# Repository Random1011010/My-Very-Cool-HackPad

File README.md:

# My Very Cool HackPad

A 6-key macropad with a rotary encoder (push-button) and a 128x32 OLED display, built around the Seeed Studio XIAO RP2040. The OLED runs an idle-animated "Luna" sprite that cycles through sit, walk, run, sleep, and work.

## About me

I'm a Grade 10 (going into Grade 11) student, I am interested in aerospace, but I wanted to get real hands-on experience with hardware and PCB design before jumping into anything bigger. This was my first full custom PCB build, so a lot of this project was just learning by doing.

## Inspiration & Challenges

I wanted something I'd actually use, not just a demo board but rather, media controls, screen brightness, and a few shortcuts I use constantly (Spotlight, screenshot, undo/redo). The OLED also mattered to me too, I didn't want it just showing static text, so it runs a small animated character instead.

Most of the challenges were on the PCB and case side, since this was my first time doing either seriously. In KiCad, I had to fix a missing net label on one of the matrix columns, and ran into alignment issues while placing components that took a while to track down. Getting the rotary encoder's footprint right was its own thing.

The case went through a full rebuild. I first modeled it with not a clue how to I would get the keys to line up with the PCB, then rebuilt it in Fusion 360, sketch by sketch, to match Hack Club's submission format, while keeping the board dimensions (84x59.5mm), switch spacing, and heatset insert placement consistent with the original.

On the firmware side, I wrote the QMK code for the matrix, the encoder (volume normally, brightness when you hold the encoder's button), and the OLED animation, I adapted an open-source Luna sprite animation to loop continuously instead of reacting to typing, since I wanted it to feel more like a little idle character than a status display.
(Hopefully it works)

## Features

- 6-key matrix (2 rows x 3 columns)
- Rotary encoder with push-button:
  - Rotate: volume up/down (default)
  - Hold + rotate: screen brightness up/down
  - Short tap: play/pause
- 128x32 I2C OLED with an idle-animated Luna sprite
- QMK firmware, fully open source

## Bill of Materials (BOM)

| Part | Qty | Unit Cost | Total | Notes |
|---|---|---|---|---|
| Seeed Studio XIAO RP2040 | 1 | $5.00 | $5.00 | Main MCU |
| Cherry MX-style switches | 6 | $0.35 | $2.10 | |
| Keycaps | 6 | $0.30 | $1.80 | |
| Rotary encoder (EC11) with push-button | 1 | $0.90 | $0.90 | |
| 128x32 I2C OLED display (SSD1306) | 1 | $5.90 | $5.90 | |
| Custom PCB | 1 | ~$5.00 | $5.00 | 2-layer, JLCPCB/similar, price for small qty |
| 3D printed case | 1 | ~$3.00 | $3.00 | Filament cost estimate |
| M3 heatset inserts | 6 | $0.10 | $0.60 | |
| Diodes | 6 | $0.05 | $0.30 | 1N4148, one per switch |
| **Total** | | | **~$24.60** | |

## Pinout

| Function | Pin |
|---|---|
| Matrix rows | GP26, GP27 |
| Matrix cols | GP29, GP0, GP3 |
| Encoder A/B | GP2, GP1 |
| Encoder switch | GP28 |
| OLED SDA | GP6 |
| OLED SCL | GP7 |

## Photos

**Exploded View**

**Schematic:**

**PCB:**

**Case:**

**Firmware**
Written in QMK. Full source is in the `firmware/` folder — see [`firmware/myverycoolpad/readme.md`](firmware/myverycoolpad/readme.md) for build/flash instructions.

**Status**
Parts haven't arrived yet, so the physical build and OLED orientation are untested. Firmware compiles cleanly with `qmk compile -kb myverycoolpad -km default`.

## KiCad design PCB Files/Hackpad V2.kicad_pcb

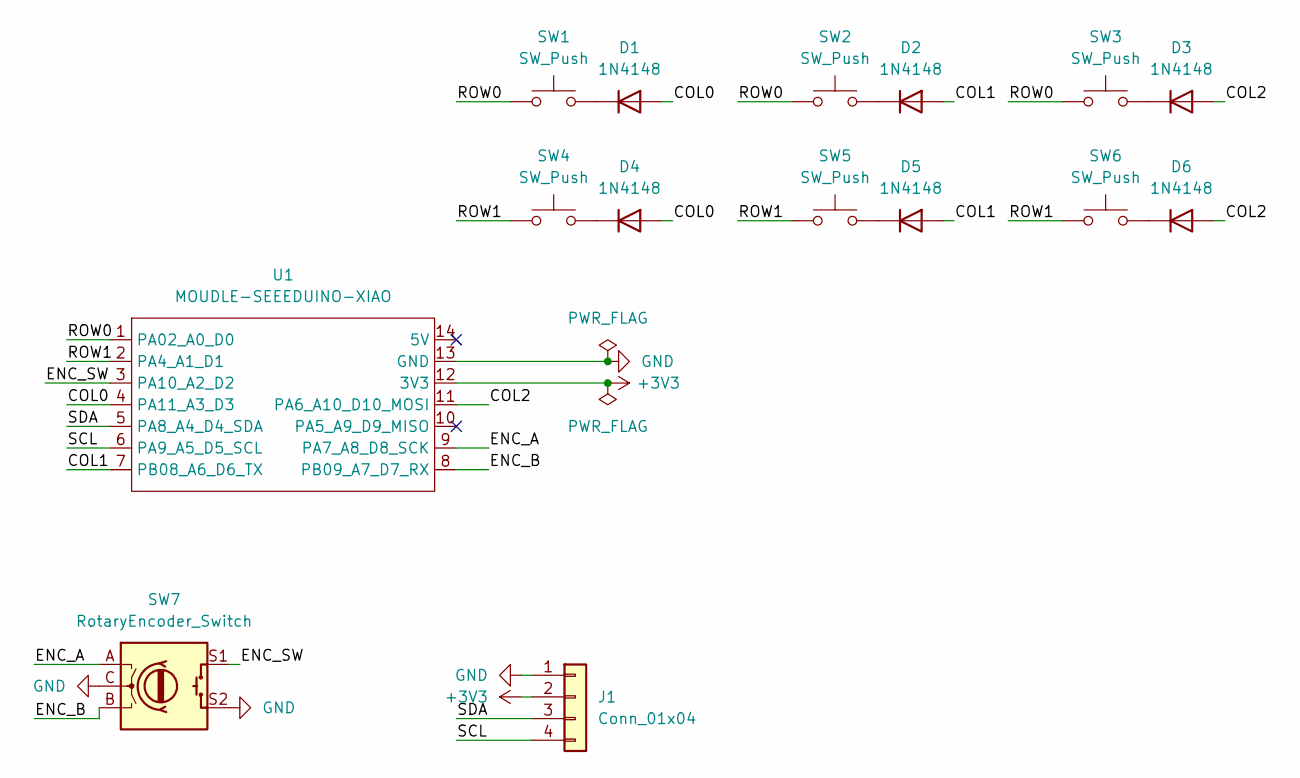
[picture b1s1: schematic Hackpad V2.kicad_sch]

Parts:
D1, D2, D3, D4, D5, D6: 1N4148; D_DO-35_SOD27_P7.62mm_Horizontal
J1: Conn_01x04; PinHeader_1x04_P2.54mm_Vertical
SW1, SW2, SW3, SW4, SW5, SW6: SW_Push; SW_Cherry_MX_1.00u_PCB
SW7: RotaryEncoder_Switch; RotaryEncoder_Alps_EC11E-Switch_Vertical_H20mm
U1: MOUDLE-SEEEDUINO-XIAO; XIAO-Generic-Hybrid-14P-2.54-21X17.8MM

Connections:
+3V3: J1.2, U1.12 (3V3)
/COL0: D1.2 (A), D4.2 (A), U1.4 (PA11_A3_D3)
/COL1: D2.2 (A), D5.2 (A), U1.7 (PB08_A6_D6_TX)
/COL2: D3.2 (A), D6.2 (A), U1.11 (PA6_A10_D10_MOSI)
/ENC_A: SW7.A, U1.9 (PA7_A8_D8_SCK)
/ENC_B: SW7.B, U1.8 (PB09_A7_D7_RX)
/ENC_SW: SW7.S1, U1.3 (PA10_A2_D2)
/ROW0: SW1.1, SW2.1, SW3.1, U1.1 (PA02_A0_D0)
/ROW1: SW4.1, SW5.1, SW6.1, U1.2 (PA4_A1_D1)
/SCL: J1.4, U1.6 (PA9_A5_D5_SCL)
/SDA: J1.3, U1.5 (PA8_A4_D4_SDA)
GND: J1.1, SW7.C, SW7.S2, U1.13 (GND)
unnamed: D1.1 (K), SW1.2
unnamed: D2.1 (K), SW2.2
unnamed: D3.1 (K), SW3.2
unnamed: D4.1 (K), SW4.2
unnamed: D5.1 (K), SW5.2
unnamed: D6.1 (K), SW6.2

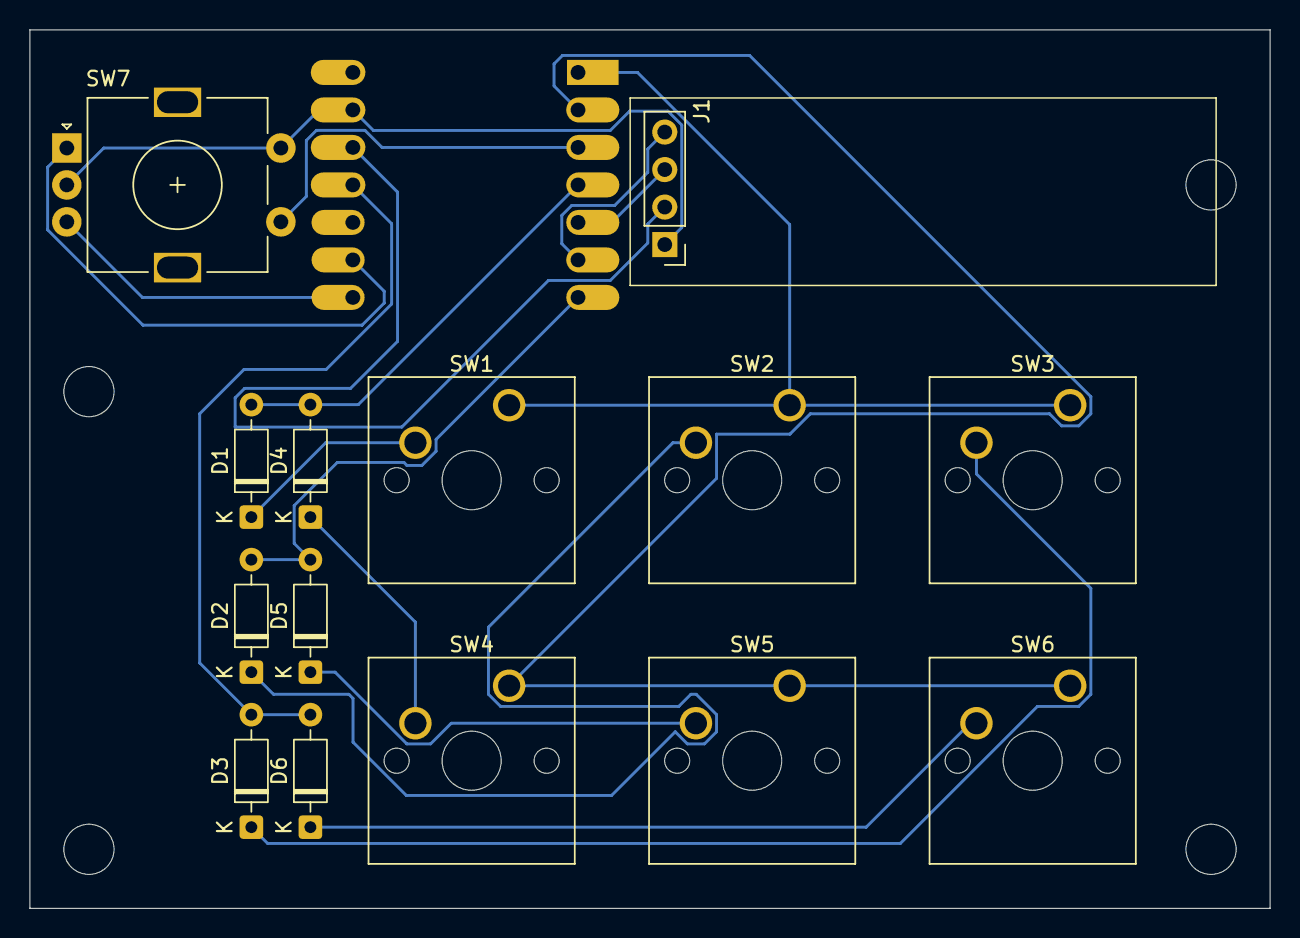
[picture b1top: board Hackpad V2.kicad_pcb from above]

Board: 2 copper layers, 84.0 x 59.5 mm, 15 parts (1 on the bottom side), 18 nets.
